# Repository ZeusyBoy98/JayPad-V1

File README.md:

# JayPad-V1
My personal multi-purpose hackpad including an oled screen, 6 buttons for different assignable functions, and a knob for volume or brightness. 

## Assembled JayPad V1

## Schematic

## PCB

## Case

## BOM

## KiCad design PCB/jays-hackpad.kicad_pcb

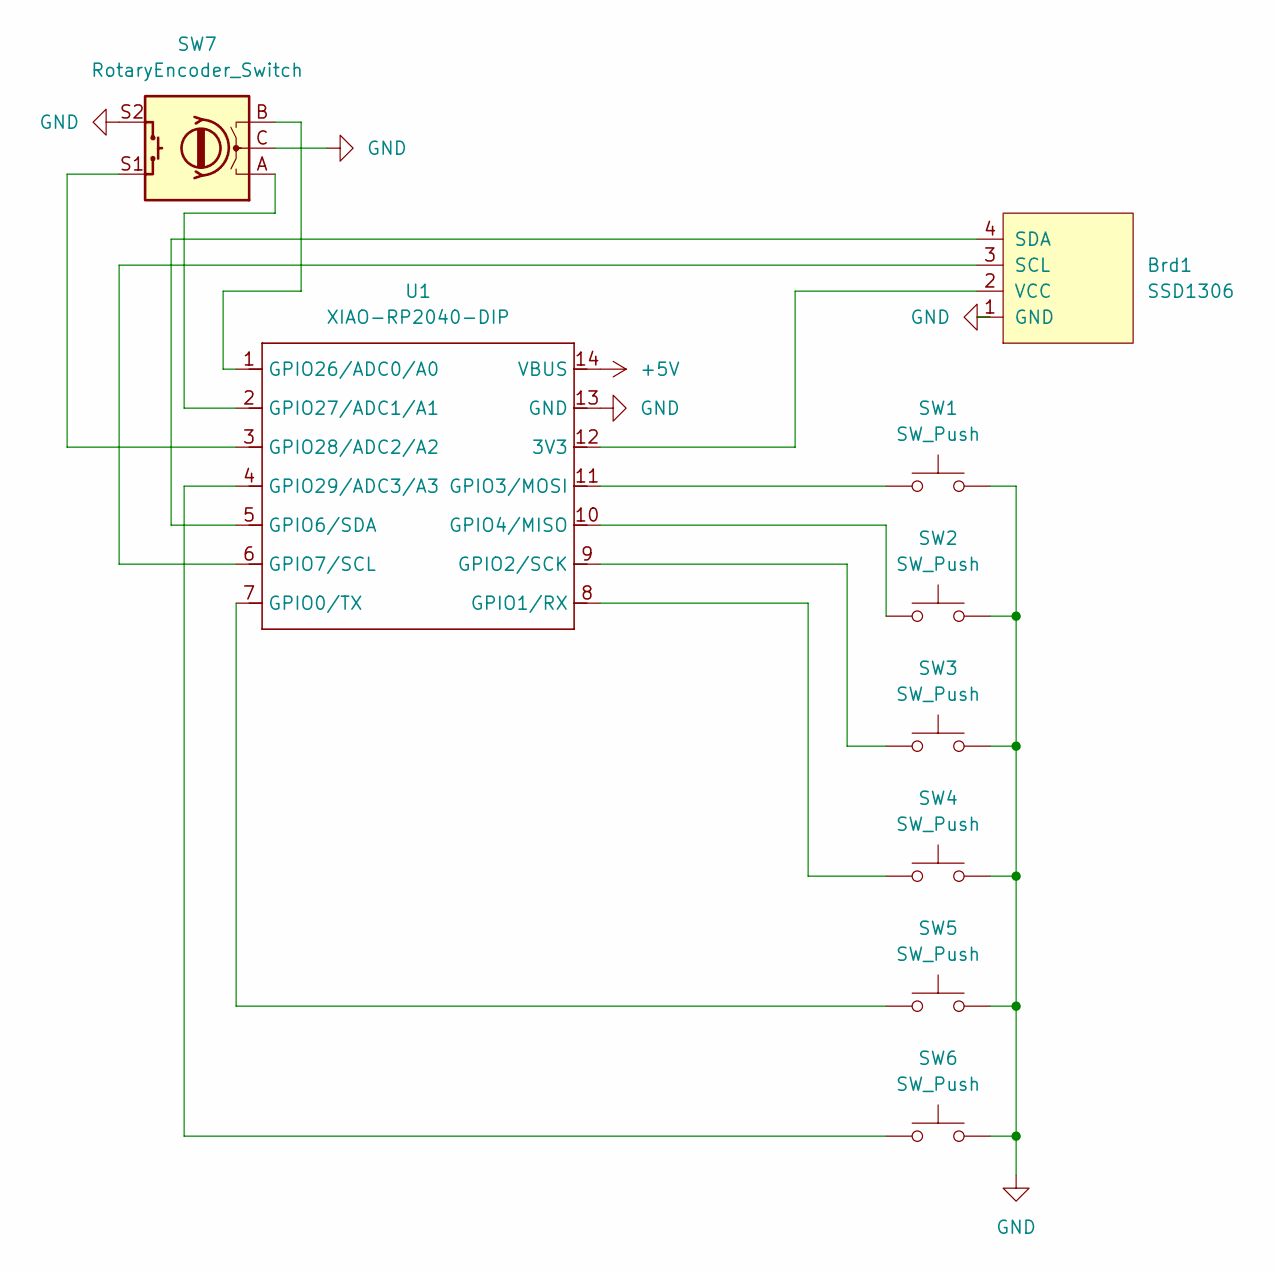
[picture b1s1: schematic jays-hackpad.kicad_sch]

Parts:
Brd1: SSD1306; SSD1306-0.91-OLED-4pin-128x32
SW1, SW2, SW3, SW4, SW5, SW6: SW_Push; SW_Cherry_MX_1.00u_PCB
SW7: RotaryEncoder_Switch; RotaryEncoder_Alps_EC11E-Switch_Vertical_H20mm
U1: XIAO-RP2040-DIP

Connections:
+5V: U1.14 (VBUS)
GND: Brd1.1 (GND), SW1.1, SW2.1, SW3.1, SW4.1, SW5.1, SW6.1, SW7.C, SW7.S2, U1.13 (GND)
unnamed: Brd1.3 (SCL), U1.6 (GPIO7/SCL)
unnamed: Brd1.4 (SDA), U1.5 (GPIO6/SDA)
unnamed: Brd1.2 (VCC), U1.12 (3V3)
unnamed: SW5.2, U1.7 (GPIO0/TX)
unnamed: SW4.2, U1.8 (GPIO1/RX)
unnamed: SW3.2, U1.9 (GPIO2/SCK)
unnamed: SW1.2, U1.11 (GPIO3/MOSI)
unnamed: SW2.2, U1.10 (GPIO4/MISO)
unnamed: SW7.B, U1.1 (GPIO26/ADC0/A0)
unnamed: SW7.A, U1.2 (GPIO27/ADC1/A1)
unnamed: SW7.S1, U1.3 (GPIO28/ADC2/A2)
unnamed: SW6.2, U1.4 (GPIO29/ADC3/A3)

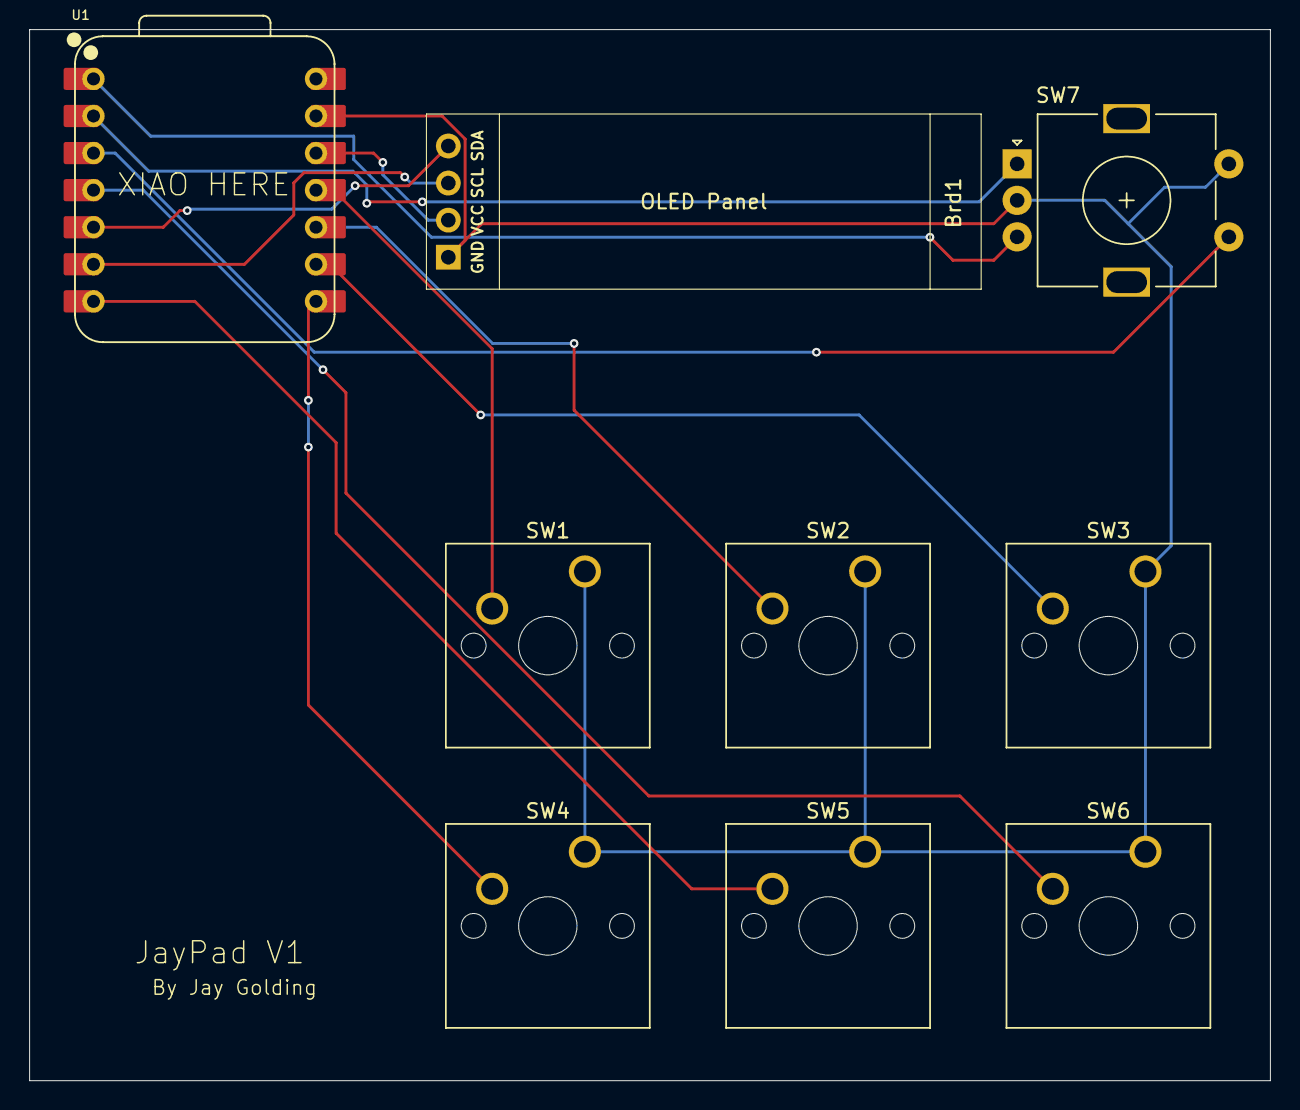
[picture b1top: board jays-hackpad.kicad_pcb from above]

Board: 2 copper layers, 85.0 x 72.0 mm, 9 parts (0 on the bottom side), 13 nets.

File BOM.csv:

Qty	Value	Footprint
1	SSD1306	SSD1306:128x64OLED
6	SW_Push	Button_Switch_Keyboard:SW_Cherry_MX_1.00u_PCB
1	RotaryEncoder_Switch	Rotary_Encoder:RotaryEncoder_Alps_EC11E-Switch_Vertical_H20mm
1	XIAO-RP2040-DIP	Seeed Studio XIAO Series Library:XIAO-RP2040-DIP

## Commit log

2025-12-17 Added CAD files
2025-12-17 Add PCB files
2025-12-17 Add Firmware file
2025-12-17 KMK makes me hate myself slightly less than QMK
2025-12-17 Add needed files
2025-12-17 Finish README
2025-12-17 Add schematic
2025-12-18 Put images into Images folder
2025-12-18 Updated Image file paths
2025-12-18 Add case parts image
2025-12-18 Case parts image is png
2025-12-18 Fixes to submit for the third time...
2025-12-18 Forgot a few fixes
2025-12-18 Fixed readme image references
2025-12-23 Gerbers
